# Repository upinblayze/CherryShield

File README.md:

# CherryShield

> This project references [this](https://learn.sparkfun.com/tutorials/cherry-mx-switch-breakout-hookup-guide?_ga=2.203788117.458645258.1494055496-431278443.1491328355) guide from [sparkfun](www.sparkfun.com)

This repository is meant to create a prototype using [cherry-mx switches](http://cherryamericas.com/product/mx-series-2/) including necessary concepts such as designing a key matrix and leveraging properties of a general purpose diode.

This project is dependent on [Sparkfun](www.sparkfun.com)'s EAGLE libraries and also OSHPark's DRU file. The EAGLE library is necessary because we use an already made cherry-mx switch footprint.

## Get EAGLE
The EAGLE download can be found [here](https://www.autodesk.com/products EAGLE/free-download). The free version is sufficient in this case
> EAGLE used to be made by CADSOFT USA, but is now under the AutoDesk umbrella.

## Download and apply design rules
We are going to be using [OSHPark's design rules](https://oshpark.com/LaenPCBOrder.dru) since this is the service we are using to make the PCBs

## Clone the repository
For the puposes of simplicity, it is recommended that you clone this repository in your $HOME (root) directory. Input the following command in terminal.

`git clone git@github.com:upinblayze/CherryShield.git`

## Download Sparkfun's EAGLE libraries
They are made for older versions of EAGLE, but they work nonetheless. You may either clone the [repository](https://github.com/sparkfun/SparkFun EAGLE-Libraries) or download the [zip file]( https://github.com/sparkfun/SparkFun EAGLE-Libraries/archive/master.zip)

## Setup EAGLE Directories

1. Options > Directories...
    * To add a paths by placing colons between each file path to where a the desired directory exists
2. To add the Sparkfun EAGLE libraries in the library field, append `:path/to/SparkFun EAGLE-Libraries-master`. In my case, since I have it in the root directory, I would append `:$HOME/SparkFun EAGLE-Libraries-master`
3. Repeat with the Project field. This is meant for if you do not have a project in the EAGLE created folder. I like to keep my git repositories in the root, so I would append `:$HOME/CherryShield` to the project field

> You _may_ want to add the DRU (design rules) directory here, however it may be more intuitive to simply use the design rules check to check against OSHPark design specifications

## Open Project

From here you open the project and click on the schematics. You can view the board also by switching view via the `SCH/BRD` button in the tool bar

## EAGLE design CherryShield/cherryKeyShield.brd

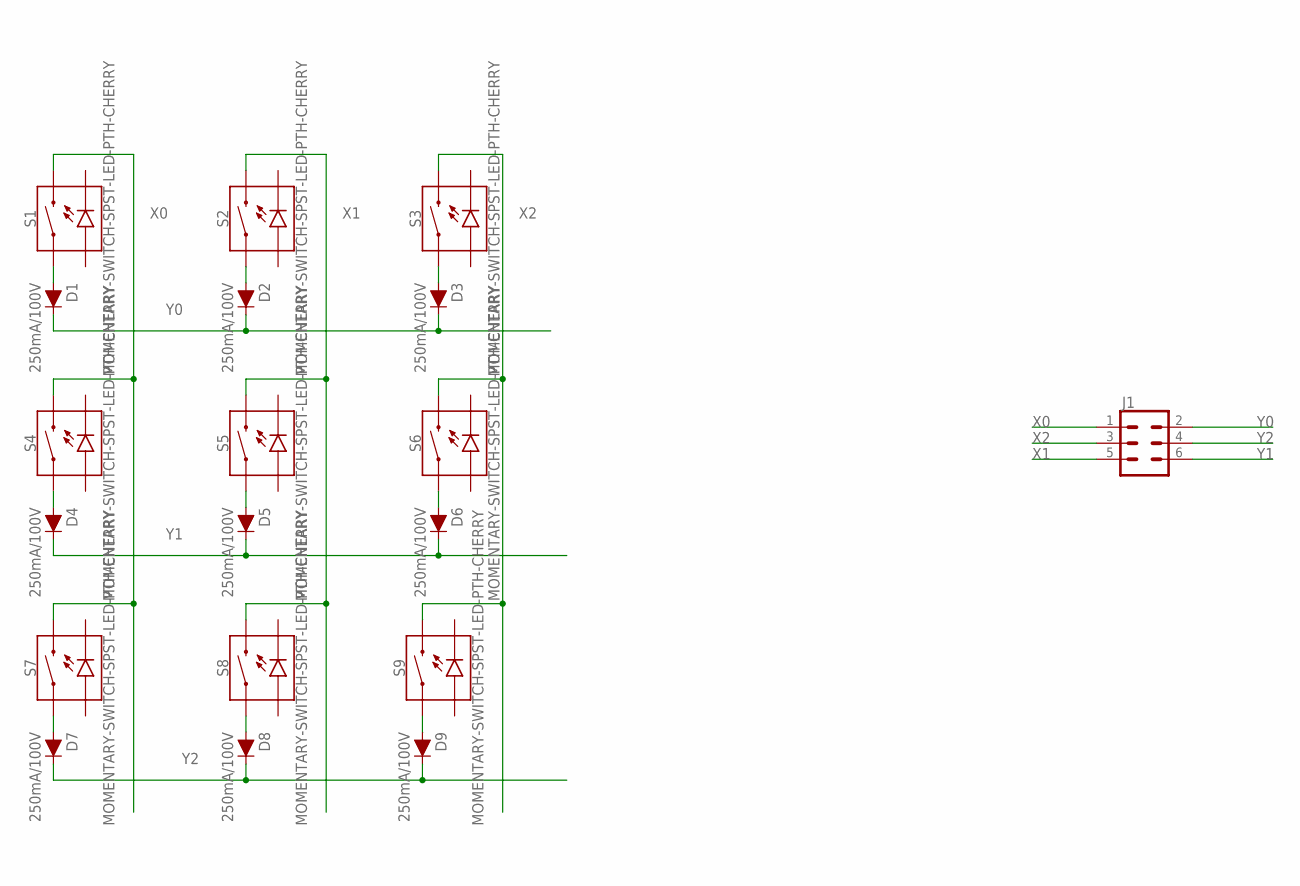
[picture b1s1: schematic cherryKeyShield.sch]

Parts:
D1, D2, D3, D4, D5, D6, D7, D8, D9: 250mA/100V; SOD-323
J1: CONN_03X22X3_SILK_MALE_PTH; 2X3
S1, S2, S3, S4, S5, S6, S7, S8, S9: MOMENTARY-SWITCH-SPST-LED-PTH-CHERRY; CHERRY-MX-LED

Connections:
unnamed: D5.A, S5.S1 (1)
unnamed: D6.A, S6.S1 (1)
unnamed: D1.A, S1.S1 (1)
unnamed: D2.A, S2.S1 (1)
unnamed: D3.A, S3.S1 (1)
unnamed: D4.A, S4.S1 (1)
unnamed: D8.A, S8.S1 (1)
unnamed: D7.A, S7.S1 (1)
unnamed: D9.A, S9.S1 (1)
X0: J1.1, S1.S2 (2), S4.S2 (2), S7.S2 (2)
X1: J1.5, S2.S2 (2), S5.S2 (2), S8.S2 (2)
X2: J1.3, S3.S2 (2), S6.S2 (2), S9.S2 (2)
Y0: D1.C, D2.C, D3.C, J1.2
Y1: D4.C, D5.C, D6.C, J1.6
Y2: D7.C, D8.C, D9.C, J1.4

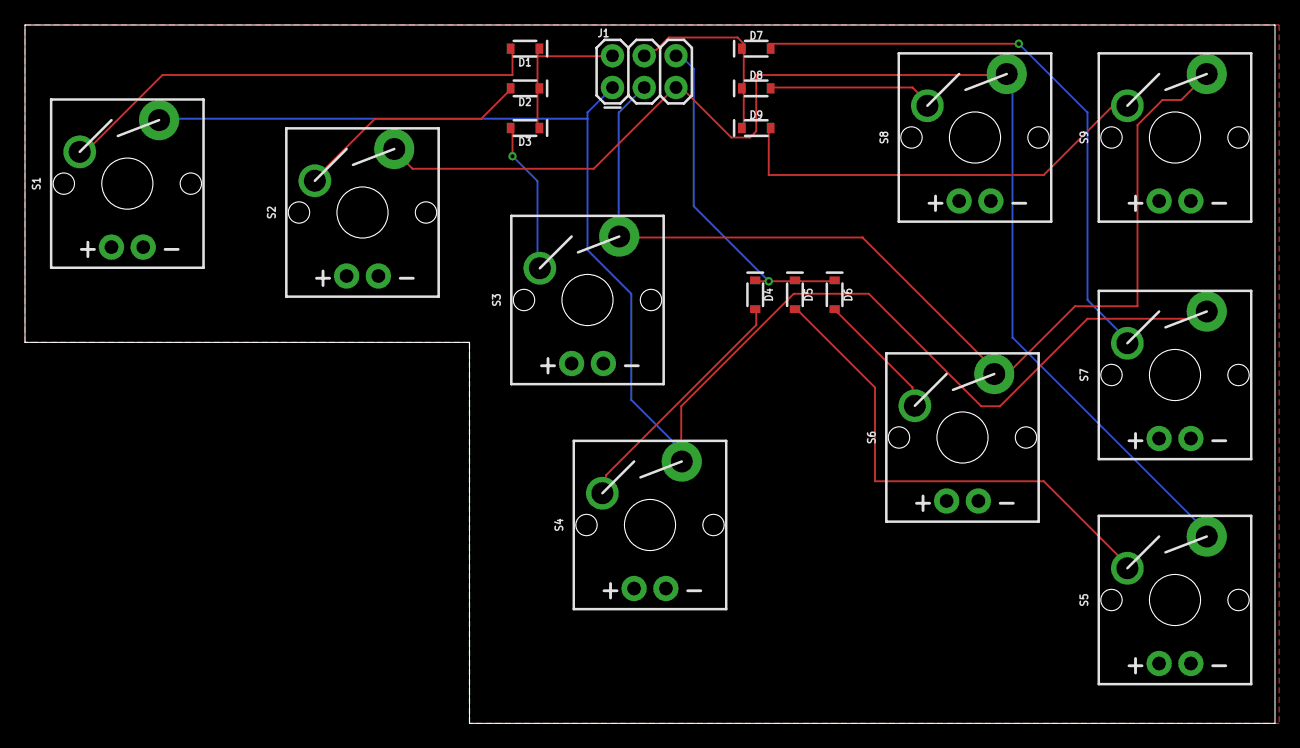
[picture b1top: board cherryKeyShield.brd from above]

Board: 2 copper layers, 100.0 x 55.9 mm, 19 parts (0 on the bottom side), 15 nets.

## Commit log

2017-05-08 early stuff
2017-05-17 newer layout
2017-06-15 final form
2017-06-18 cleanup
2017-06-19 minimized size for cost
2017-08-14 Working arduino code
2017-08-14 updated gitignore

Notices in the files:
parts and their libraries:
SparkFun-DiscreteSemi: Licensing: Creative Commons ShareAlike 4.0 International - https://creativecommons.org/licenses/by-sa/4.0
